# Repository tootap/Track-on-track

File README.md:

# Track-on-track

This is our ECE 477 senior design project.

Track-on-Track is a project which helps users to find their belongings. It is placed with a user’s belonging and uses a GSM module to connect with a phone app which shows the location of the device. A smartphone application will be available to allow the user to interact with the device but it can also be interacted with through GSM.  When the device is in shorter range, it uses a bluetooth module and shows on the app whether the user is getting closer to the device. The user will be able to see the device’s location, activate a sound alarm on the device, and manipulate the devices settings remotely. The user will also be able to interact with the device’s settings through various buttons and an LCD on the device.

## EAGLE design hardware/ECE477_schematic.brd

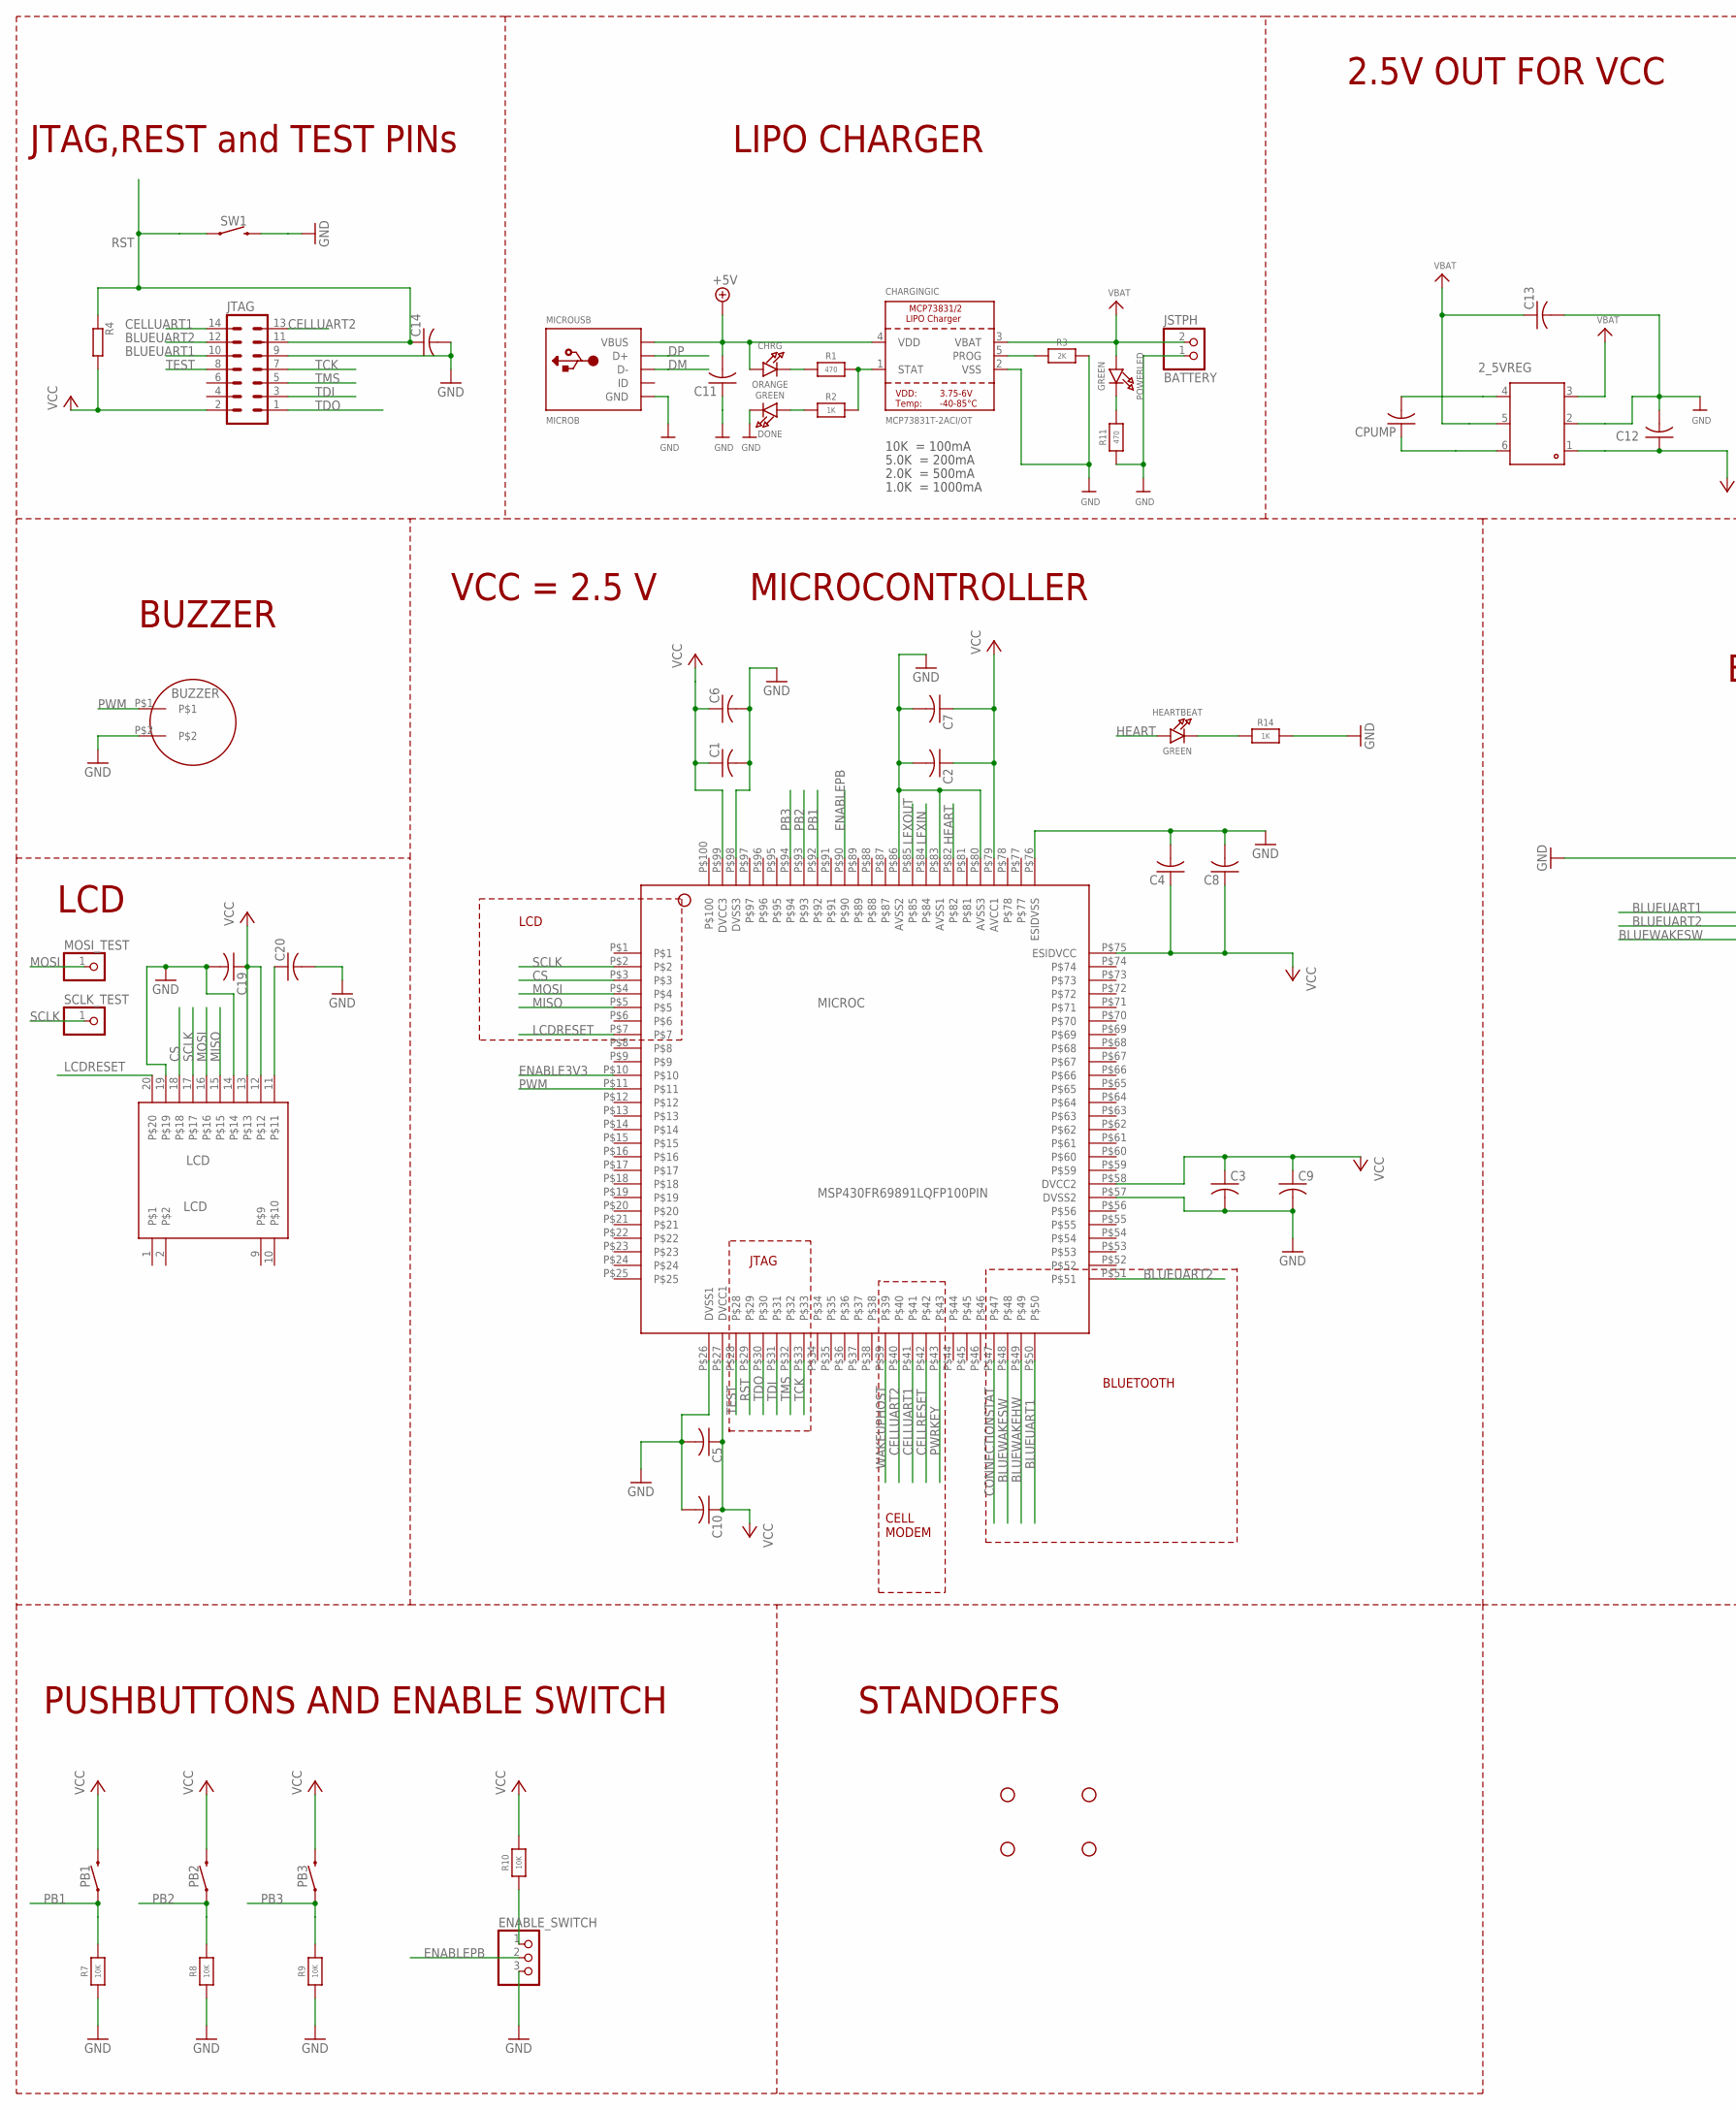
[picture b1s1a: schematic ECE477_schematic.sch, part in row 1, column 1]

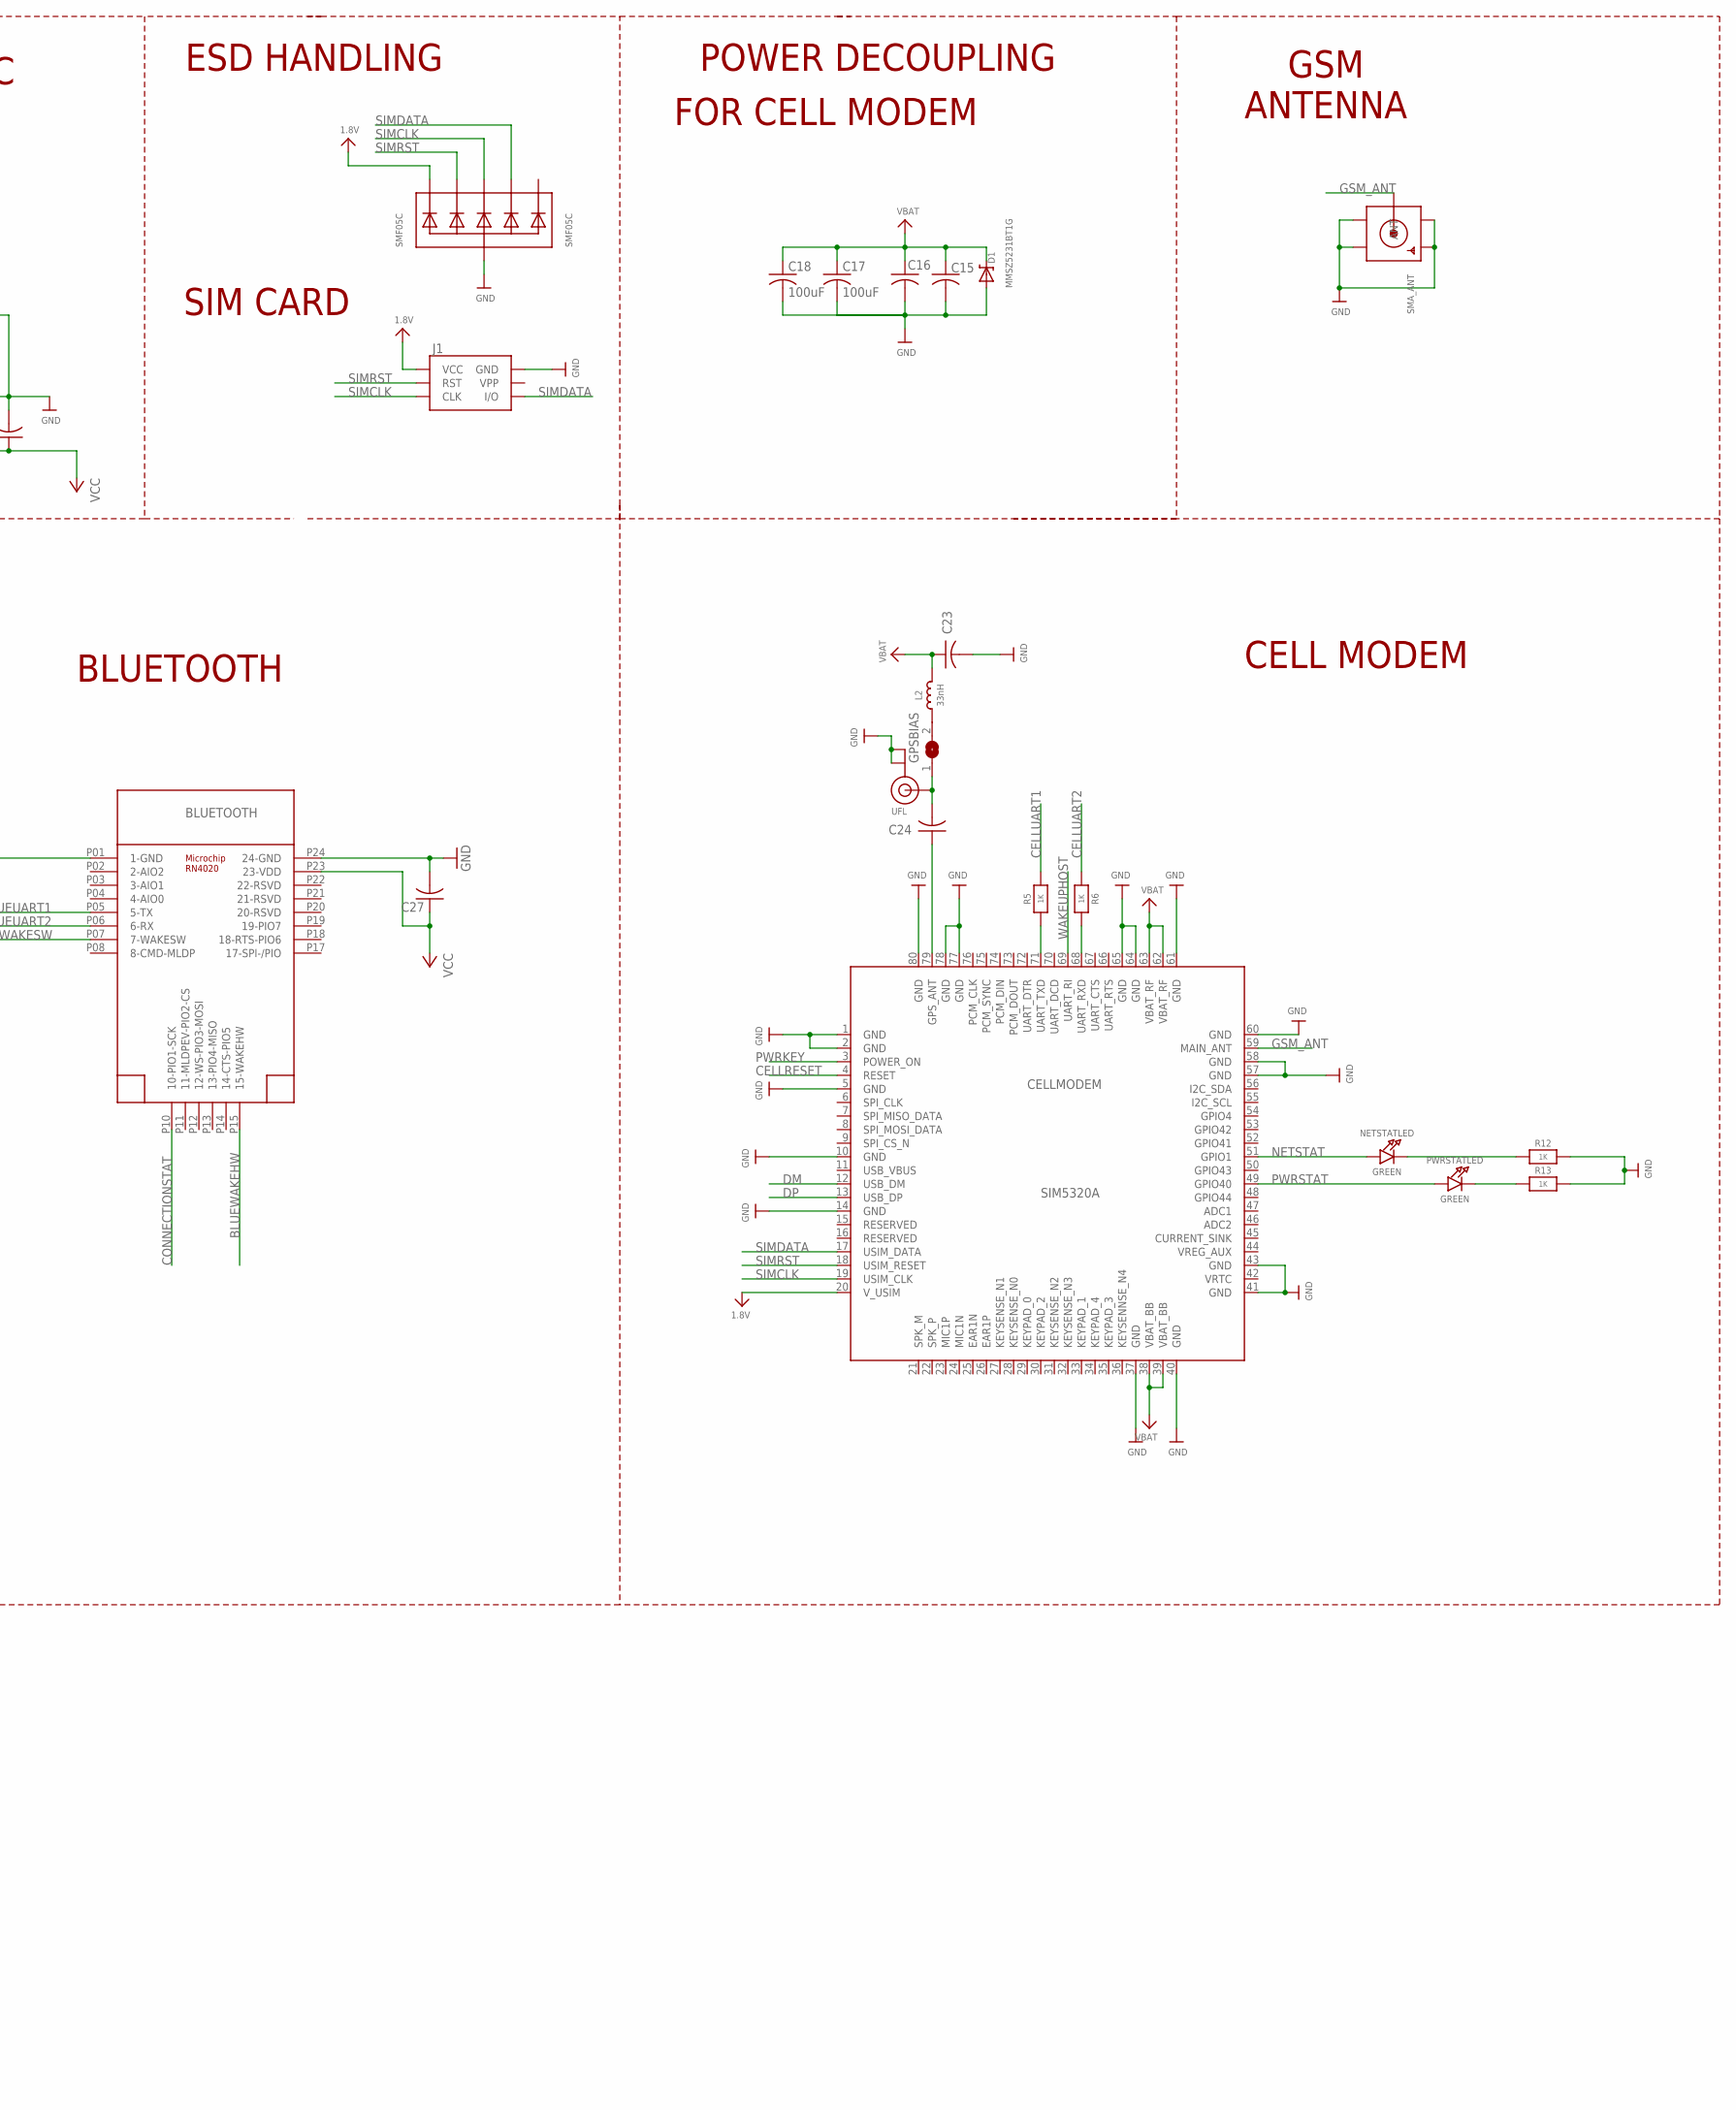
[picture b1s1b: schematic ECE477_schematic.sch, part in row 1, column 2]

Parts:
2_5VREG: 2_5VREG; REG710NASOC6
BATTERY: JSTPH; JSTPH2
BLUETOOTH: RN4020; RN4020SMD
BUZZER: BUZZER; BUZZERTHROUGHHOLE
C1, C2, C3, C4, C5, C6, C7, C8, C9, C10, C11, C12, C13, C14, C15, C16, C19, C20, C23, C24, C27: C-USC1206; C1206
C17, C18: 100uF; C1210
CELLMODEM: SIM5320A; MICROBUILDER_SIM5320
CHARGINGIC: MCP73831T-2ACI/OT; SOT23-5
CHRG: ORANGE; CHIPLED_0805_NOOUTLINE
CPUMP: C-USC1206; C1206
D1: MMSZ5231BT1G; SOD-123
DONE: GREEN; CHIPLED_0805_NOOUTLINE
ENABLE_SWITCH: PINHD-1X3; 1X03
GPSBIAS: SOLDERJUMPER; SOLDERJUMPER_ARROW_NOPASTE
H1, H2, H3, H4: STAND-OFF
HEARTBEAT: GREEN; CHIPLED_0805_NOOUTLINE
J1: SIMHOLDERSIM; SIMHOLDER
JTAG: CON-ML_ML14
L2: 33nH; _0805MP
LCD: LCD; LCDTHROUGHHOLE
MICROC: MSP430FR69891LQFP100PIN; MSP430FR69891
MICROUSB: MICROB; ZX62DB5PA8(30)
MOSI_TEST: PINHD-1X1; 1X01
NETSTATLED: GREEN; CHIPLED_0805_NOOUTLINE
PB1, PB2, PB3: MOMENTARY-SWITCH-SPST-PTH-6.0MM; TACTILE_SWITCH_PTH_6.0MM
POWERLED: GREEN; CHIPLED_0805_NOOUTLINE
PWRSTATLED: GREEN; CHIPLED_0805_NOOUTLINE
R1, R11: 470; 0805-NO
R2, R5, R6, R12, R13, R14: 1K; 0805-NO
R3: 2K; 0805-NO
R4: SMD_R_0805; SMD_0805
R7, R8, R9, R10: 10K; 0805-NO
SCLK_TEST: PINHD-1X1; 1X01
SMA_ANT: MICROBUILDER_SMACONNECTOR_EDGE; MICROBUILDER_SMA_EDGELAUNCH
SMF05C: SMF05C; SOT363
SW1: MOMENTARY-SWITCH-SPST-PTH-6.0MM; TACTILE_SWITCH_PTH_6.0MM
UFL: MICROBUILDER_ANTENNA_U.FL; MICROBUILDER_U.FL

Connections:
1.8V: CELLMODEM.20 (V_USIM), J1.C1 (VCC), SMF05C.1 (C1)
+5V: C11.2, CHARGINGIC.4 (VDD), CHRG.A, MICROUSB.+5V (VBUS)
BLUEUART1: BLUETOOTH.P05 (5-TX), JTAG.10, MICROC.P$50
BLUEUART2: BLUETOOTH.P06 (6-RX), JTAG.12, MICROC.P$51
BLUEWAKEHW: BLUETOOTH.P15 (15-WAKEHW), MICROC.P$49
BLUEWAKESW: BLUETOOTH.P07 (7-WAKESW), MICROC.P$48
CELLRESET: CELLMODEM.4 (RESET), MICROC.P$42
CELLUART1: JTAG.14, MICROC.P$41, R5.2
CELLUART2: JTAG.13, MICROC.P$40, R6.2
CONNECTIONSTAT: BLUETOOTH.P10 (10-PIO1-SCK), MICROC.P$47
CS: LCD.18, MICROC.P$3
DM: CELLMODEM.12 (USB_DM), MICROUSB.D-
DP: CELLMODEM.13 (USB_DP), MICROUSB.D+
ENABLE3V3: MICROC.P$10
ENABLEPB: ENABLE_SWITCH.2, MICROC.P$90
GND: 2_5VREG.2, BATTERY.1, BLUETOOTH.P01 (1-GND), BLUETOOTH.P24 (24-GND), BUZZER.P$2, C1.2, C2.2, C3.2, C4.2, C5.2, C6.2, C7.2, C8.2, C9.2, C10.2, C11.1, C12.2, C13.2, C14.2, C15.2, C16.2, C17.2, C18.2, C19.2, C20.2, C23.2, C27.2, CELLMODEM.1 (GND), CELLMODEM.2 (GND), CELLMODEM.5 (GND), CELLMODEM.10 (GND), CELLMODEM.14 (GND), CELLMODEM.37 (GND), CELLMODEM.40 (GND), CELLMODEM.41 (GND), CELLMODEM.43 (GND), CELLMODEM.57 (GND), CELLMODEM.58 (GND), CELLMODEM.60 (GND), CELLMODEM.61 (GND), CELLMODEM.64 (GND), CELLMODEM.65 (GND), CELLMODEM.77 (GND), CELLMODEM.78 (GND), CELLMODEM.80 (GND), CHARGINGIC.2 (VSS), D1.A, DONE.C, ENABLE_SWITCH.3, J1.C5 (GND), JTAG.9, LCD.14, LCD.19, MICROC.P$26 (DVSS1), MICROC.P$57 (DVSS2), MICROC.P$76 (ESIDVSS), MICROC.P$80 (AVSS3), MICROC.P$83 (AVSS1), MICROC.P$86 (AVSS2), MICROC.P$98 (DVSS3), MICROUSB.GND, R3.2, R7.1, R8.1, R9.1, R11.1, R12.2, R13.2, R14.2, SMA_ANT.GND@1 (GND4), SMA_ANT.GND@2 (GND3), SMA_ANT.GND@3 (GND2), SMA_ANT.GND@4 (GND1), SMF05C.2 (A), SW1.3 (2), UFL.1 (GND), UFL.2 (GND)
GSM_ANT: CELLMODEM.59 (MAIN_ANT), SMA_ANT.P (ANT)
HEART: HEARTBEAT.A, MICROC.P$82
LCDRESET: LCD.20, MICROC.P$7
LFXIN: MICROC.P$84
LFXOUT: MICROC.P$85
MISO: LCD.15, MICROC.P$5
MOSI: LCD.16, MICROC.P$4, MOSI_TEST.1
unnamed: CHRG.C, R1.1
unnamed: CHARGINGIC.1 (STAT), R1.2, R2.2
unnamed: C20.1, LCD.11
unnamed: 2_5VREG.4, CPUMP.2
unnamed: CHARGINGIC.5 (PROG), R3.1
unnamed: DONE.A, R2.1
unnamed: 2_5VREG.6, CPUMP.1
unnamed: C24.1, CELLMODEM.79 (GPS_ANT)
unnamed: C24.2, GPSBIAS.1, UFL.3 (SIGNAL)
unnamed: CELLMODEM.71 (UART_TXD), R5.1
unnamed: CELLMODEM.68 (UART_RXD), R6.1
unnamed: POWERLED.C, R11.2
unnamed: NETSTATLED.C, R12.1
unnamed: ENABLE_SWITCH.1, R10.1
unnamed: PWRSTATLED.C, R13.1
unnamed: GPSBIAS.2, L2.1
unnamed: HEARTBEAT.C, R14.1
NETSTAT: CELLMODEM.51 (GPIO1), NETSTATLED.A
PB1: MICROC.P$92, PB1.1, R7.2
PB2: MICROC.P$93, PB2.1, R8.2
PB3: MICROC.P$94, PB3.1, R9.2
PWM: BUZZER.P$1, MICROC.P$11
PWRKEY: CELLMODEM.3 (POWER_ON), MICROC.P$43
PWRSTAT: CELLMODEM.49 (GPIO40), PWRSTATLED.A
RST: C14.1, JTAG.11, MICROC.P$29, R4.1, SW1.1
SCLK: LCD.17, MICROC.P$2, SCLK_TEST.1
SIMCLK: CELLMODEM.19 (USIM_CLK), J1.C3 (CLK), SMF05C.4 (C3)
SIMDATA: CELLMODEM.17 (USIM_DATA), J1.C7 (I/O), SMF05C.5 (C4)
SIMRST: CELLMODEM.18 (USIM_RESET), J1.C2 (RST), SMF05C.3 (C2)
TCK: JTAG.7, MICROC.P$33
TDI: JTAG.3, MICROC.P$31
TDO: JTAG.1, MICROC.P$30
TEST: JTAG.8, MICROC.P$28
TMS: JTAG.5, MICROC.P$32
VBAT: 2_5VREG.3, 2_5VREG.5, BATTERY.2, C13.1, C15.1, C16.1, C17.1, C18.1, C23.1, CELLMODEM.38 (VBAT_BB), CELLMODEM.39 (VBAT_BB), CELLMODEM.62 (VBAT_RF), CELLMODEM.63 (VBAT_RF), CHARGINGIC.3 (VBAT), D1.C, L2.2, POWERLED.A
VCC: 2_5VREG.1, BLUETOOTH.P23 (23-VDD), C1.1, C2.1, C3.1, C4.1, C5.1, C6.1, C7.1, C8.1, C9.1, C10.1, C12.1, C19.1, C27.1, JTAG.2, LCD.12, LCD.13, MICROC.P$27 (DVCC1), MICROC.P$58 (DVCC2), MICROC.P$75 (ESIDVCC), MICROC.P$79 (AVCC1), MICROC.P$99 (DVCC3), PB1.3 (2), PB2.3 (2), PB3.3 (2), R4.2, R10.2
WAKEUPHOST: CELLMODEM.69 (UART_RI), MICROC.P$39

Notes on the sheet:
10K = 100mA
5.0K = 200mA
2.0K = 500mA
1.0K = 1000mA
LIPO CHARGER
2.5V OUT FOR VCC
JTAG,REST and TEST PINs
SIM CARD
POWER DECOUPLING
GSM ANTENNA
LCD
ESD HANDLING
BLUETOOTH
JTAG
CELL MODEM
CELL MODEM
BUZZER
MICROCONTROLLER
PUSHBUTTONS AND ENABLE SWITCH
VCC = 2.5 V
STANDOFFS
FOR CELL MODEM

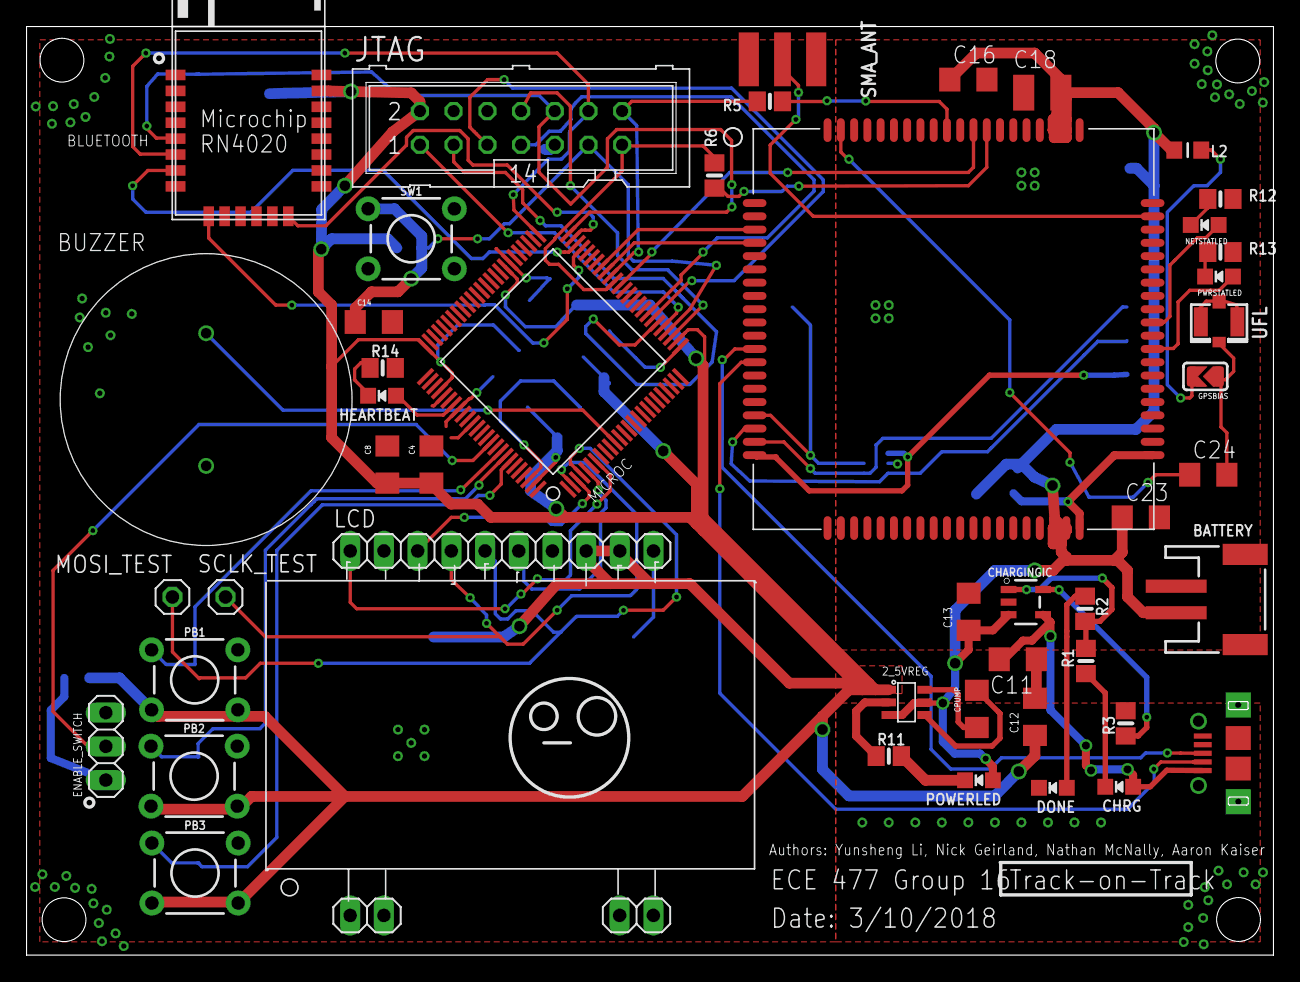
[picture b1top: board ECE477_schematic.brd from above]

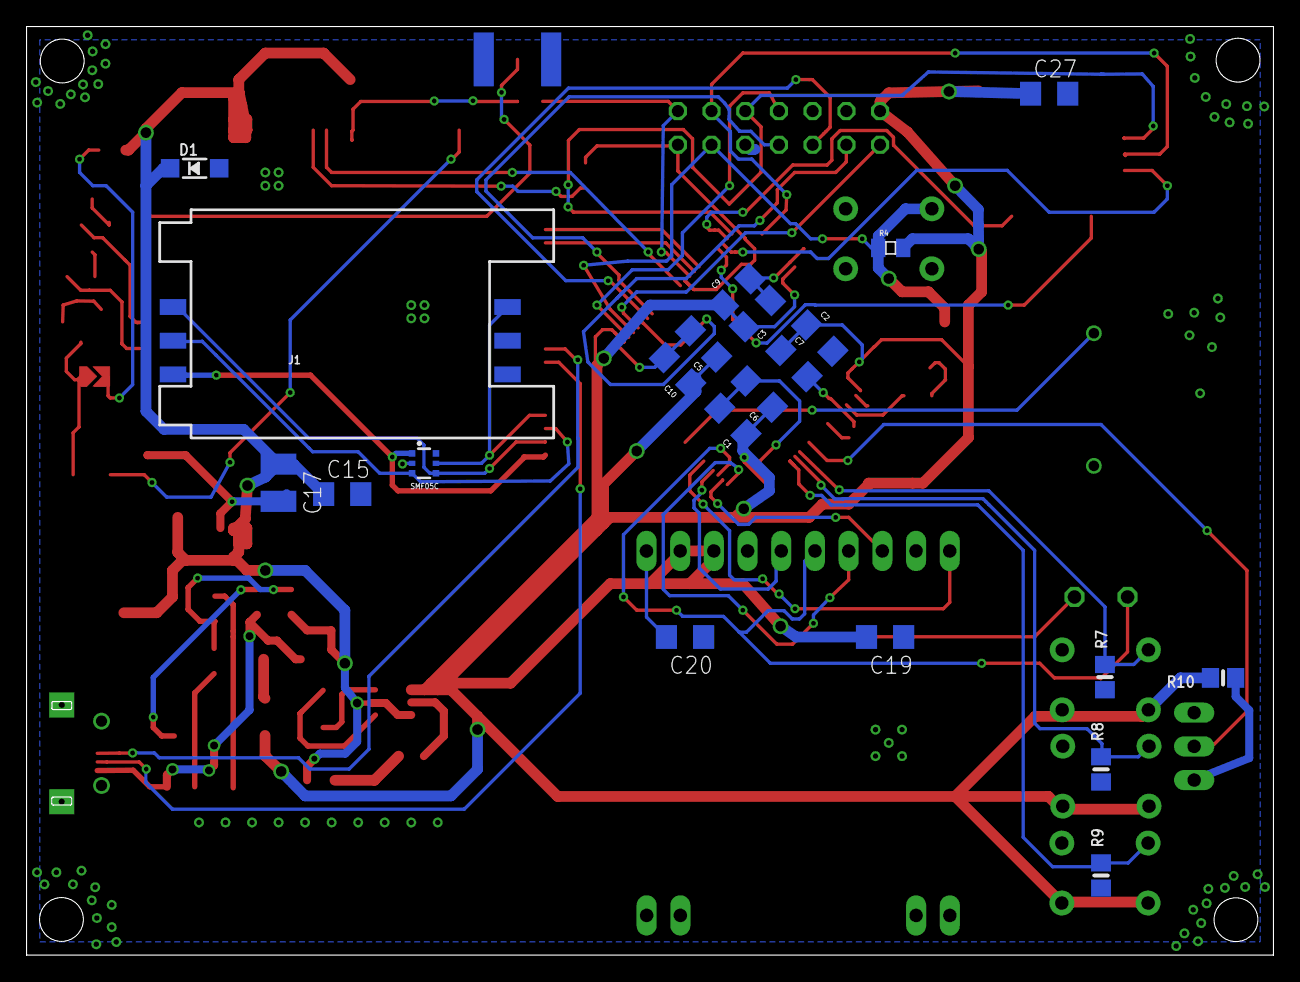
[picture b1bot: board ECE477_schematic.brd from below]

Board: 2 copper layers, 94.0 x 70.0 mm, 72 parts (21 on the bottom side), 57 nets.

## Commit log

2018-02-15 Making directories
2018-02-21 adding parts library
2018-02-21 readme
2018-02-21 added part of SIM5320
2018-02-22 adding the schematic
2018-02-22 basic communication with GSM
2018-02-23 Prototype app, can send and receive SMS messages
2018-03-02 adding the schematic and brd file from week 8 (midterm review)
2018-03-10 the ordered PCB schematic and layout files
2018-03-21 cleaned up firmware with better gsm functionality
2018-03-30 03/29/2018 image of schematic
2018-04-09 Delete slac668h.zip
    Not a direct component of the project
2018-04-18 Add files via upload
    contains semi-working bluetooth code
2018-04-18 Adding app with UI
2018-04-19 Adding all current app files
2018-04-27 Updating app with most functionality
2018-04-30 confirmed to be the latest
2018-04-30 Finishing up app
2018-04-30 Adding zip of app
2018-04-30 Adding homework files
2018-04-30 new firmware
2018-04-30 Updating string manipulation for GPS coords
2018-05-01 the lcd is working!

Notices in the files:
parts and their libraries:
microbuilder: This work is placed in the public domain, and may be freely used for commercial and non-commercial work with the following conditions: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
SparkFun-Hardware: Licensing: Creative Commons ShareAlike 4.0 International - https://creativecommons.org/licenses/by-sa/4.0
